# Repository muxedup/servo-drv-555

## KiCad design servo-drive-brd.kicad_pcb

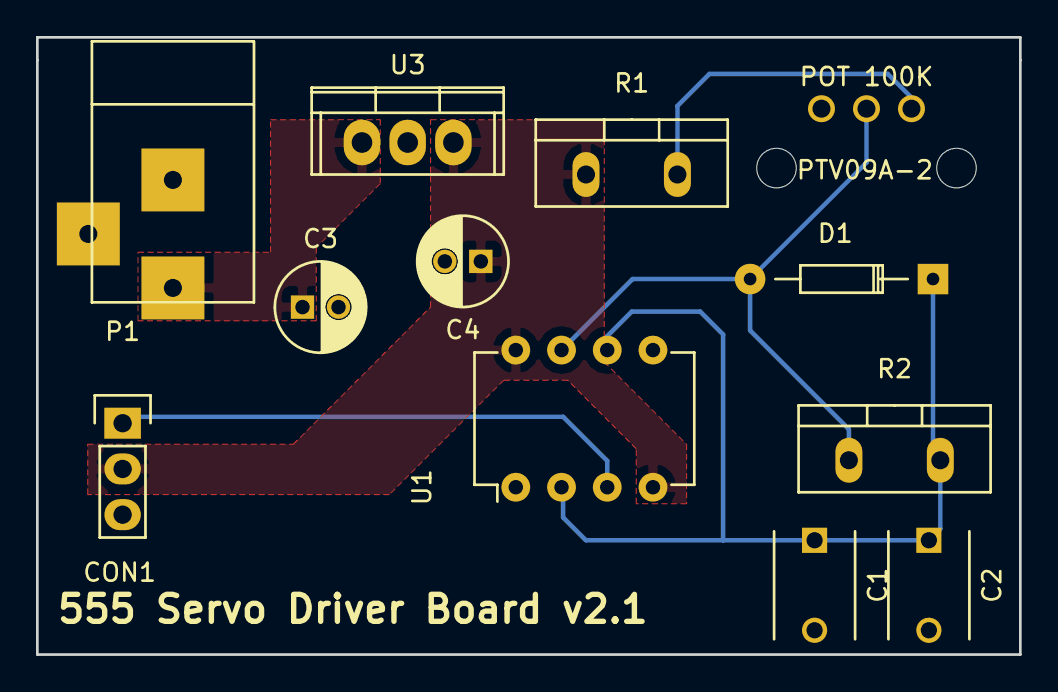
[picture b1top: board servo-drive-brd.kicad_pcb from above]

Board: 2 copper layers, 54.6 x 34.3 mm, 12 parts (0 on the bottom side), 7 nets.

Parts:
C1, C2: 10 n; C_Disc_D6_P5
C3, C4: 10 uF; C_Radial_D5_L11_P2
CON1: BARREL_JACK
D1: 1N4148; Diode_DO-35_SOD27_Horizontal_RM10
P1: CONN_01X03; Pin_Header_Straight_1x03
PTV09A-2: POT 100K; PTV09A-2-TOP
R1: 56K; Resistor_TO-220_Vertical
R2: 1.6M; Resistor_TO-220_Vertical
U1: LM555N; DIP-8_W7.62mm
U3: LM7805CT; TO-220

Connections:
+5V: C4.1, P1.2, R1.1, U1.4, U1.8, U3.3
GND: C1.2, C2.2, C3.2, C4.2, CON1.2, CON1.3, P1.3, U1.1, U3.2
unnamed: C1.1, C2.1, D1.1, R2.2, U1.2, U1.6
unnamed: C3.1, CON1.1, U3.1
unnamed: D1.2, PTV09A-2.2, R2.1, U1.7
unnamed: P1.1, U1.3
unnamed: PTV09A-2.1, R1.2

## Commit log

2016-01-29 Initial schematic and layout for a 1 sided board
2016-01-29 Add gerber files and pcb layout
2016-03-03 Final version (hopefully, fingers crossed) with a linear power regulator, and a horizontally mounted pot (facing the right way)
